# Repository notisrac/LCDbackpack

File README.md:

# LCD Backpack (serial/I2C)

[Arduino](https://www.arduino.cc/) based character LCD driver circuit, with a form factor that lets it be mounted to the back of a display.
It can be used with any [Hitachi HD44780](https://en.wikipedia.org/wiki/Hitachi_HD44780_LCD_controller) based LCD, or compatible VFD displays (ex.: [Noritake-Itron VFDs](http://www.noritake-itron.com/NewWeb/GVFD/Overview/Overview.asp)).
Supports displays with a single row (1x16) or double row (2x8) connectors.
The display is controlled through a [74HC595](http://www.nxp.com/documents/data_sheet/74HC_HCT595.pdf) shift register.

## Features
* Supports any Hitachi HD44780 based character LCD (or VFD)
* 1x16 and 2x8 pins
* Arduino compatible device with most of the GPIO pins accessible
* Serial and [I2C](https://en.wikipedia.org/wiki/I%C2%B2C) ports
* [FTDI](https://www.adafruit.com/product/284) and (6 pin) [ICSP](https://en.wikipedia.org/wiki/In-system_programming) programming ports
* On-board voltage regulator
* Contrast pot
* Backlight controllable from code (QC pin on the shift register)
* It is the same size as a 16x2 character LCD (also the mounting holes line up)

## Ports
* Serial (D0, D1)
* I2C (A4, A5)
* FTDI header
* ICSP

## Usable Arduino GPIO pins
* Analog: A0, A1, A2, A3, A4, A5
* Digital: D2, D3, D4, D5, D6, D7, D8, D9, D12

## Power supply
The board has an on board power connector, that powers the backpack and the display too.
You can use a voltage regulator like the [LD1117](http://www.st.com/web/en/resource/technical/document/datasheet/CD00000544.pdf), or if you have a regulated power supply, you can just leave it unpopulated and short pins 2 and 3 together.

## Shift register pinout
* QA  - Not connected 
* QB  - LCD RS
* QC  - LCD Backlight control
* QD  - LCD E
* QE  - LCD DB4
* QF  - LCD DB5
* QG  - LCD DB6
* QH  - LCD DB7
* QH* - Not connected
* SER - Arduino D11
* SCK - Arduino D13
* RCK - Arduino D10

## Errata
* Due to the fact, that the enable line of the display is tied to one of the shift register pins, this construction does not work with any of the standard libraries. You need to use the provided library to drive the display!
* In the first version of the board layout the isolation of the ground fill was set to 0. This could have caused a short.

## Pictures
Assembled:

Schematic:

*Made with Cadsoft Eagle v6.5.0*

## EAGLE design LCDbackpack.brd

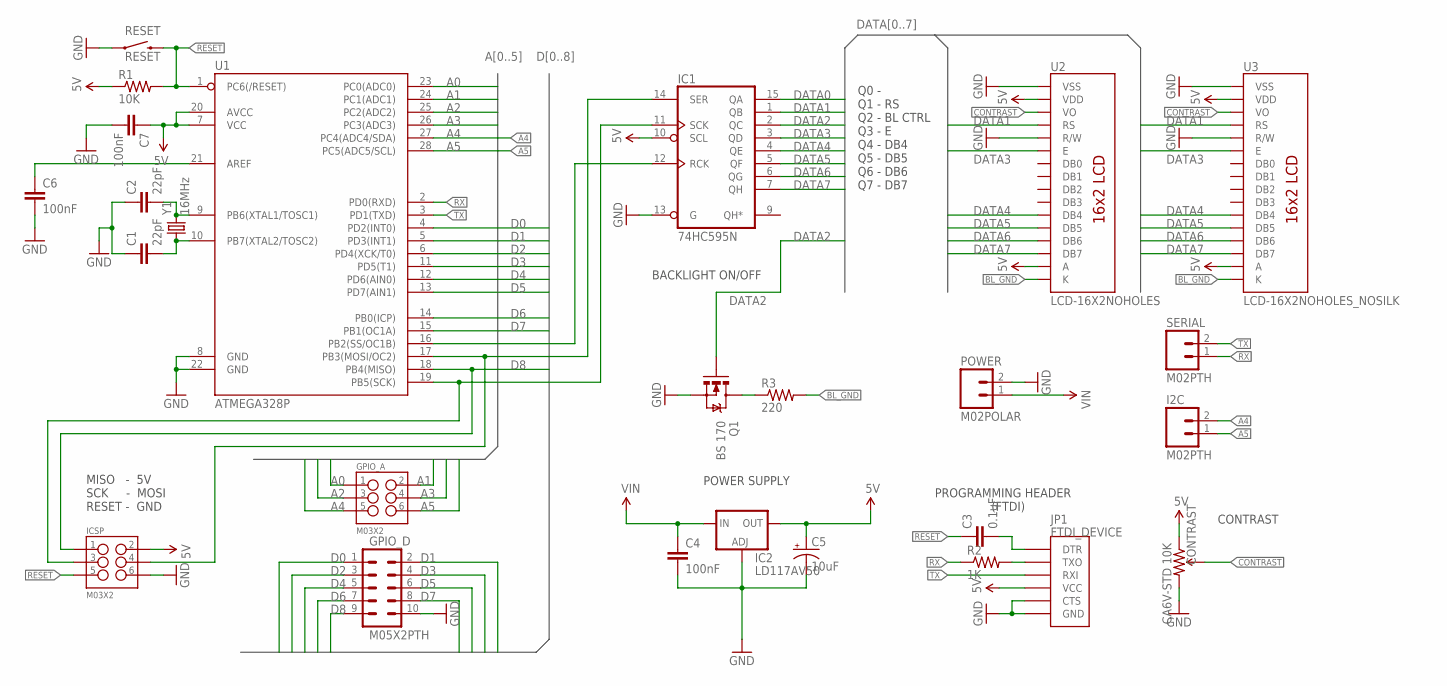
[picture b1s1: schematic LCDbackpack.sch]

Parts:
C1, C2: 22pF; CAP-PTH-SMALL2
C3: 0.1uF; CAP-PTH-SMALL2
C4, C6, C7: 100nF; CAP-PTH-SMALL2
C5: 10uF; CPOL-RADIAL-10UF-25V
CONTRAST: CA6V-STD 10K; TRIM_POT_PTH
GPIO_A: M03X2; 2X3
GPIO_D: M05X2PTH; AVR_ICSP
I2C: M02PTH; 1X02
IC1: 74HC595N; DIL16
IC2: LD117AV50; TO220L1
ICSP: M03X2; 2X3_POGO
JP1: FTDI_DEVICE; FTDI_DEVICE_SIDE
POWER: M02POLAR; MOLEX-1X2
Q1: BS 170; TO-92
R1: 10K; AXIAL-0.3
R2: 1K; AXIAL-0.3
R3: 220; AXIAL-0.3
RESET: RESET; TACTILE-PTH
SERIAL: M02PTH; 1X02
U1: ATMEGA328P; DIL28-3
U2: LCD-16X2NOHOLES; LCD-16X2_NOHOLES
U3: LCD-16X2NOHOLES_NOSILK; LCD-8X2_NOHOLES_NOSILK
Y1: 16MHz; HC49US

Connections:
A0: GPIO_A.1, U1.23 (PC0(ADC0))
A1: GPIO_A.2, U1.24 (PC1(ADC1))
A2: GPIO_A.3, U1.25 (PC2(ADC2))
A3: GPIO_A.4, U1.26 (PC3(ADC3))
A4: GPIO_A.5, I2C.2, U1.27 (PC4(ADC4/SDA))
A5: GPIO_A.6, I2C.1, U1.28 (PC5(ADC5/SCL))
BL_GND: R3.P$2 (2), U2.16 (K), U3.16 (K)
CONTRAST: CONTRAST.2 (WIPER), U2.3 (VO), U3.3 (VO)
D0: GPIO_D.1, U1.4 (PD2(INT0))
D1: GPIO_D.2, U1.5 (PD3(INT1))
D2: GPIO_D.3, U1.6 (PD4(XCK/T0))
D3: GPIO_D.4, U1.11 (PD5(T1))
D4: GPIO_D.5, U1.12 (PD6(AIN0))
D5: GPIO_D.6, U1.13 (PD7(AIN1))
D6: GPIO_D.7, U1.14 (PB0(ICP))
D7: GPIO_D.8, U1.15 (PB1(OC1A))
D8: GPIO_D.9, ICSP.P$1 (1), U1.18 (PB4(MISO))
DATA0: IC1.15 (QA)
DATA1: IC1.1 (QB), U2.4 (RS), U3.4 (RS)
DATA2: IC1.2 (QC), Q1.2 (G)
DATA3: IC1.3 (QD), U2.6 (E), U3.6 (E)
DATA4: IC1.4 (QE), U2.11 (DB4), U3.11 (DB4)
DATA5: IC1.5 (QF), U2.12 (DB5), U3.12 (DB5)
DATA6: IC1.6 (QG), U2.13 (DB6), U3.13 (DB6)
DATA7: IC1.7 (QH), U2.14 (DB7), U3.14 (DB7)
GND: C1.1, C2.1, C4.2, C5.2 (-), C6.2, C7.2, CONTRAST.3 (CW), GPIO_D.10, IC1.8 (GND), IC1.13 (G), IC2.1 (ADJ), ICSP.P$6 (6), JP1.P$5 (CTS), JP1.P$6 (GND), POWER.2, Q1.1 (S), RESET.1, U1.8 (GND), U1.22 (GND), U2.1 (VSS), U2.5 (R/W), U3.1 (VSS), U3.5 (R/W)
unnamed: C3.2, JP1.P$1 (DTR)
unnamed: JP1.P$2 (TXO), R2.P$2 (2)
unnamed: C2.2, U1.9 (PB6(XTAL1/TOSC1)), Y1.2
unnamed: C1.2, U1.10 (PB7(XTAL2/TOSC2)), Y1.1
unnamed: IC1.14 (SER), ICSP.P$4 (4), U1.17 (PB3(MOSI/OC2))
unnamed: Q1.3 (D), R3.P$1 (1)
unnamed: IC1.12 (RCK), U1.16 (PB2(SS/OC1B))
unnamed: IC1.11 (SCK), ICSP.P$3 (3), U1.19 (PB5(SCK))
unnamed: C6.1, U1.21 (AREF)
RESET: C3.1, ICSP.P$5 (5), R1.P$2 (2), RESET.3 (2), U1.1 (PC6(/RESET))
RX: R2.P$1 (1), SERIAL.1, U1.2 (PD0(RXD))
TX: JP1.P$3 (RXI), SERIAL.2, U1.3 (PD1(TXD))
VCC: C5.1 (+), C7.1, CONTRAST.1 (CCW), IC1.10 (SCL), IC1.16 (VCC), IC2.2 (OUT), ICSP.P$2 (2), JP1.P$4 (VCC), R1.P$1 (1), U1.7 (VCC), U1.20 (AVCC), U2.2 (VDD), U2.15 (A), U3.2 (VDD), U3.15 (A)
VIN: C4.1, IC2.3 (IN), POWER.1

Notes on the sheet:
POWER SUPPLY
PROGRAMMING HEADER (FTDI)
CONTRAST
BACKLIGHT ON/OFF
Q0 - Q1 - RS Q2 - BL CTRL Q3 - E Q4 - DB4 Q5 - DB5 Q6 - DB6 Q7 - DB7
MISO - 5V SCK - MOSI RESET - GND

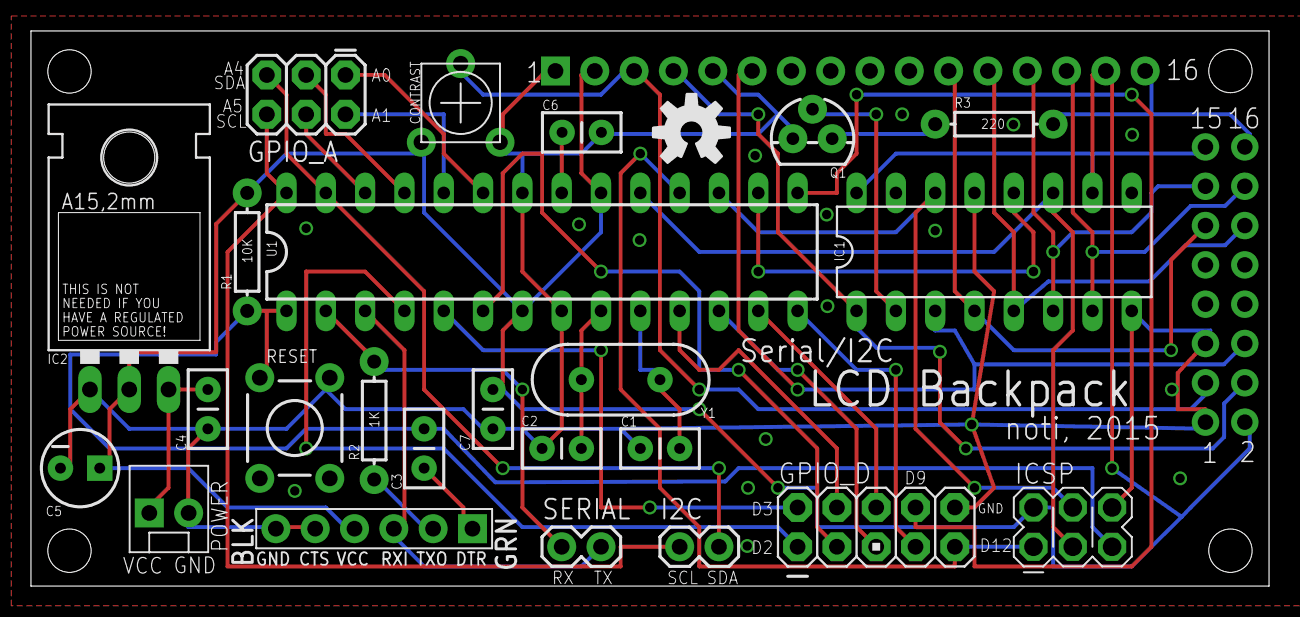
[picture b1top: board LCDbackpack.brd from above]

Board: 2 copper layers, 80.0 x 35.9 mm, 27 parts (1 on the bottom side), 39 nets.

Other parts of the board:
U$1: OSHW-LOGO-M

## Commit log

2016-05-07 Fixed isolation distance and created a library for the display
    - Fixed: the isolation distance on the ground fill was set to 0, which could cause a short
    - Added: Arduino library for driving the LCD
2018-07-27 Fixed README issues
2018-07-27 Rename LCDBackpackLib/examples/LCDBackpackTest.ino to LCDBackpackLib/examples/LCDBackpackTest/LCDBackpackTest.ino
2018-07-28 Added GA beacon to the README

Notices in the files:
parts and their libraries:
SparkFun-DigitalIC: Licensing: Creative Commons ShareAlike 4.0 International - https://creativecommons.org/licenses/by-sa/4.0
